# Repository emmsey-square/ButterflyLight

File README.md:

# ButterflyLight
Butterfly-shaped keychain thing with addressable leds

### Front PCB with decorative silkscreen and solder mask cutouts

### Back PCB with components and battery holder

### Schematic for back PCB

## Design Choices 
* CH32V003 in SOIC 8 package-low cost, great SDk courtesy of cnLohr: [ch32fun](https://github.com/cnlohr/ch32fun)
* CR2032 battery holder on back
* Switching regulator to convert battery voltage to suitable 5V for leds

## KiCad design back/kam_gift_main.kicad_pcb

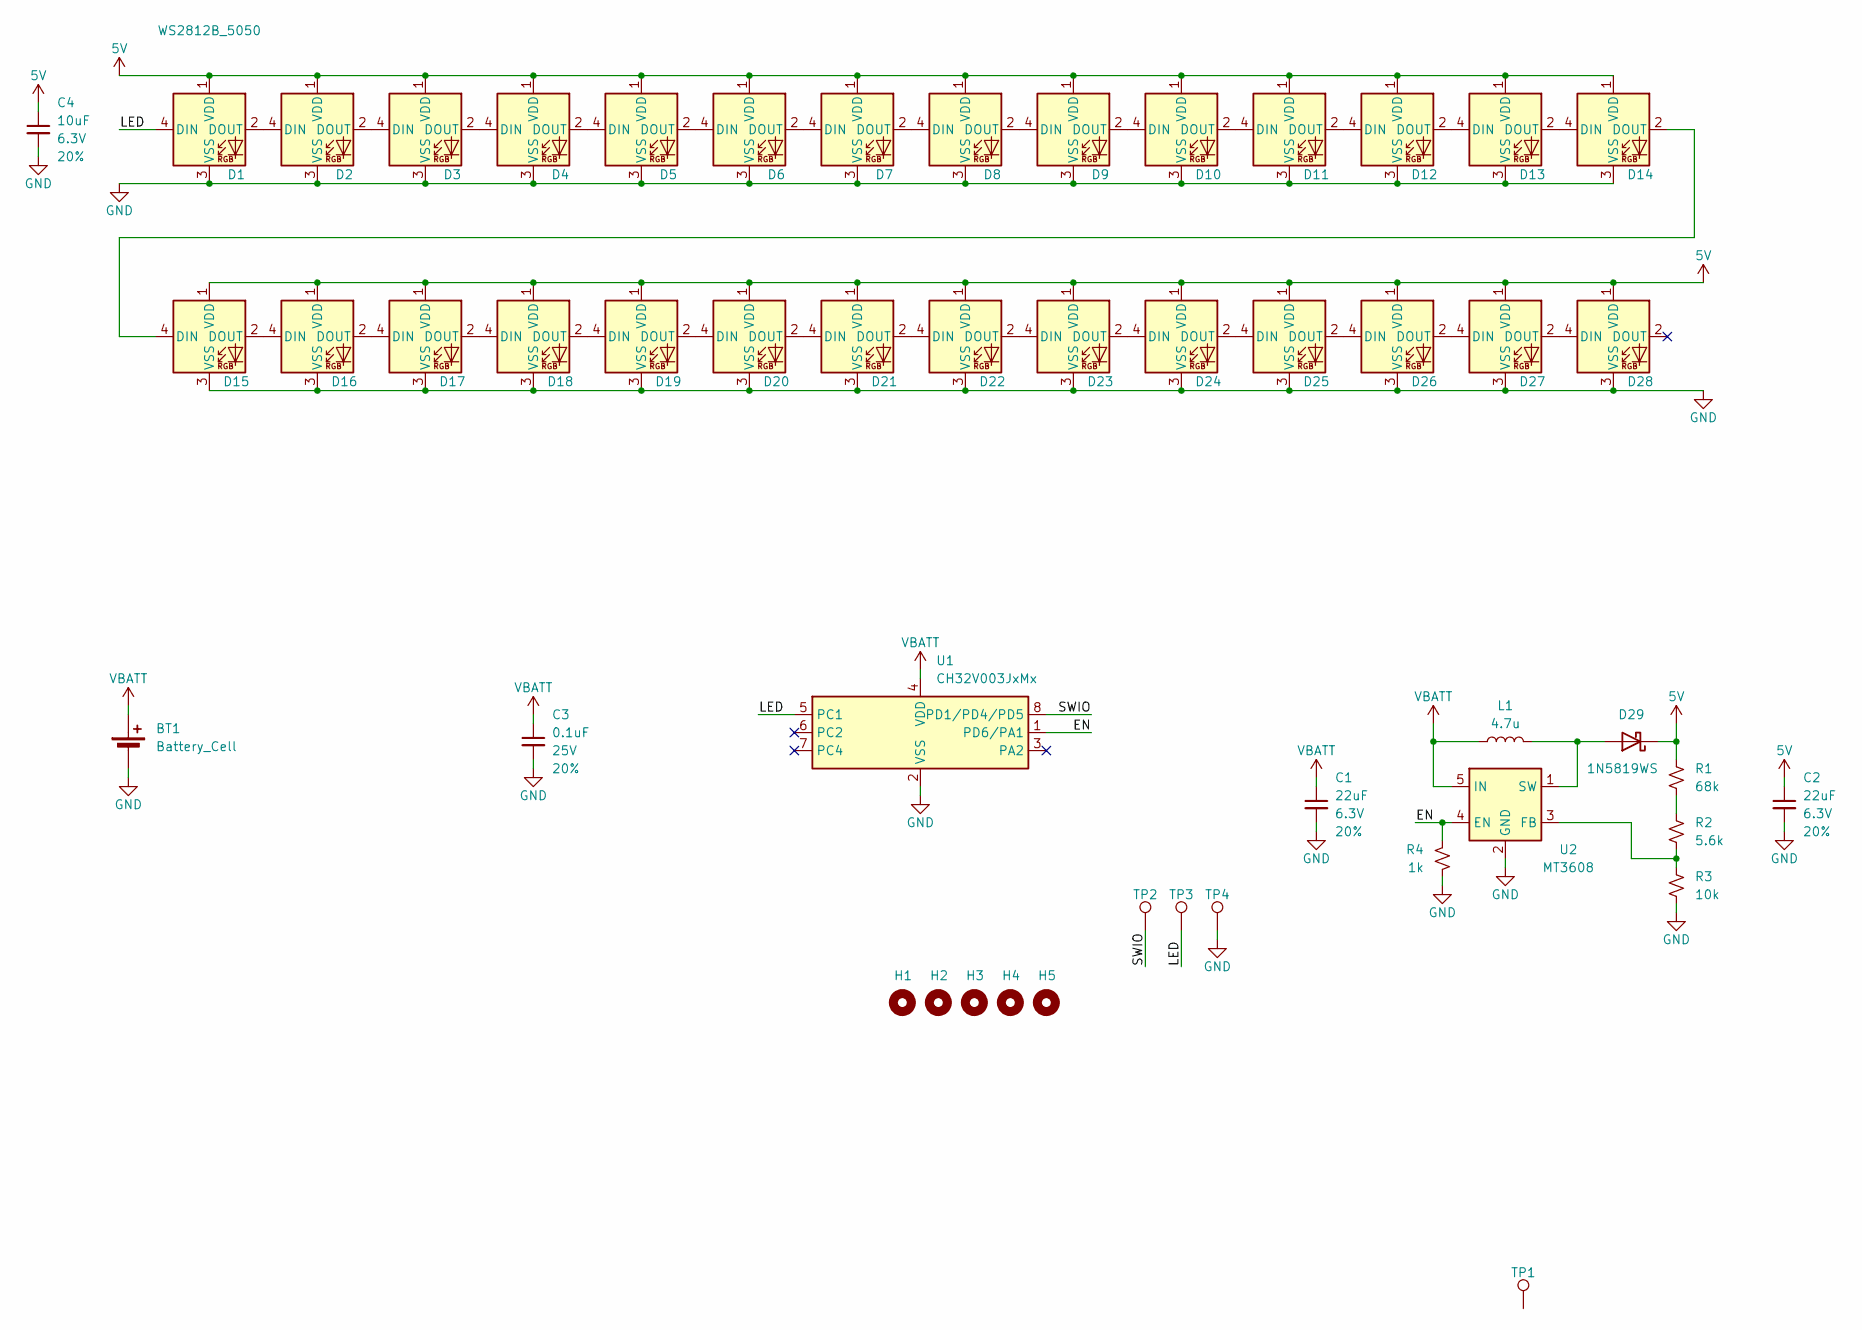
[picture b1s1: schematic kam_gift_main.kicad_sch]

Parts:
BT1: Battery_Cell; BatteryHolder_Multicomp_BC-2001_1x2032
C1, C2: 22uF; C_0603_1608Metric; Voltage 6.3V; Tolerance 20%
C3: 0.1uF; C_0603_1608Metric; Voltage 25V; Tolerance 20%
C4: 10uF; C_0603_1608Metric; Voltage 6.3V; Tolerance 20%
D1, D2, D3, D4, D5, D6, D7, D8, D9, D10, D11, D12, D13, D14, D15, D16, D17, D18, D19, D20, D21, D22, D23, D24, D25, D26, D27, D28: WS2812B_5050; LED_WS2812B_PLCC4_5.0x5.0mm_P3.2mm
D29: 1N5819WS; D_SOD-323_HandSoldering
H1, H2, H3, H4: MountingHole; MountingHole_3.2mm_M3
H5: MountingHole; MountingHole_2.2mm_M2
L1: 4.7u; L_1206_3216Metric_Pad1.22x1.90mm_HandSolder
R1: 68k; R_0603_1608Metric
R2: 5.6k; R_0603_1608Metric
R3: 10k; R_0603_1608Metric
R4: 1k; R_0603_1608Metric
TP1, TP2, TP3, TP4: 1.25mm; TestPoint_Pad_D3.0mm
U1: CH32V003JxMx; JEITA_SOIC-8_3.9x4.9mm_P1.27mm
U2: MT3608; SOT-23-6

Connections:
5V: C2.1, C4.1, D1.1 (VDD), D2.1 (VDD), D3.1 (VDD), D4.1 (VDD), D5.1 (VDD), D6.1 (VDD), D7.1 (VDD), D8.1 (VDD), D9.1 (VDD), D10.1 (VDD), D11.1 (VDD), D12.1 (VDD), D13.1 (VDD), D14.1 (VDD), D15.1 (VDD), D16.1 (VDD), D17.1 (VDD), D18.1 (VDD), D19.1 (VDD), D20.1 (VDD), D21.1 (VDD), D22.1 (VDD), D23.1 (VDD), D24.1 (VDD), D25.1 (VDD), D26.1 (VDD), D27.1 (VDD), D28.1 (VDD), D29.1 (K), R1.2
/EN: R4.2, U1.1 (PD6/PA1), U2.4 (EN)
/LED: D1.4 (DIN), TP3.1, U1.5 (PC1); also elsewhere on the board
/SWIO: TP2.1, U1.8 (PD1/PD4/PD5); also elsewhere on the board
GND: BT1.2 (-), C1.2, C2.2, C3.2, C4.2, D1.3 (VSS), D2.3 (VSS), D3.3 (VSS), D4.3 (VSS), D5.3 (VSS), D6.3 (VSS), D7.3 (VSS), D8.3 (VSS), D9.3 (VSS), D10.3 (VSS), D11.3 (VSS), D12.3 (VSS), D13.3 (VSS), D14.3 (VSS), D15.3 (VSS), D16.3 (VSS), D17.3 (VSS), D18.3 (VSS), D19.3 (VSS), D20.3 (VSS), D21.3 (VSS), D22.3 (VSS), D23.3 (VSS), D24.3 (VSS), D25.3 (VSS), D26.3 (VSS), D27.3 (VSS), D28.3 (VSS), R3.1, R4.1, TP4.1, U1.2 (VSS), U2.2 (GND); also elsewhere on the board
unnamed: D1.2 (DOUT), D2.4 (DIN)
unnamed: D2.2 (DOUT), D3.4 (DIN)
unnamed: D3.2 (DOUT), D4.4 (DIN)
unnamed: D4.2 (DOUT), D5.4 (DIN)
unnamed: D5.2 (DOUT), D6.4 (DIN)
unnamed: D6.2 (DOUT), D7.4 (DIN)
unnamed: D7.2 (DOUT), D8.4 (DIN)
unnamed: D8.2 (DOUT), D9.4 (DIN)
unnamed: D9.2 (DOUT), D10.4 (DIN)
unnamed: D10.2 (DOUT), D11.4 (DIN)
unnamed: D11.2 (DOUT), D12.4 (DIN)
unnamed: D12.2 (DOUT), D13.4 (DIN)
unnamed: D13.2 (DOUT), D14.4 (DIN)
unnamed: D14.2 (DOUT), D15.4 (DIN)
unnamed: D15.2 (DOUT), D16.4 (DIN)
unnamed: D16.2 (DOUT), D17.4 (DIN)
unnamed: D17.2 (DOUT), D18.4 (DIN)
unnamed: D18.2 (DOUT), D19.4 (DIN)
unnamed: D19.2 (DOUT), D20.4 (DIN)
unnamed: D20.2 (DOUT), D21.4 (DIN)
unnamed: D21.2 (DOUT), D22.4 (DIN)
unnamed: D22.2 (DOUT), D23.4 (DIN)
unnamed: D23.2 (DOUT), D24.4 (DIN)
unnamed: D24.2 (DOUT), D25.4 (DIN)
unnamed: D25.2 (DOUT), D26.4 (DIN)
unnamed: D26.2 (DOUT), D27.4 (DIN)
unnamed: D27.2 (DOUT), D28.4 (DIN)
unnamed: D29.2 (A), L1.2, U2.1 (SW)
unnamed: R1.1, R2.2
unnamed: R2.1, R3.2, U2.3 (FB)
VBATT: BT1.1 (+), C1.1, C3.1, L1.1, U1.4 (VDD), U2.5 (IN)

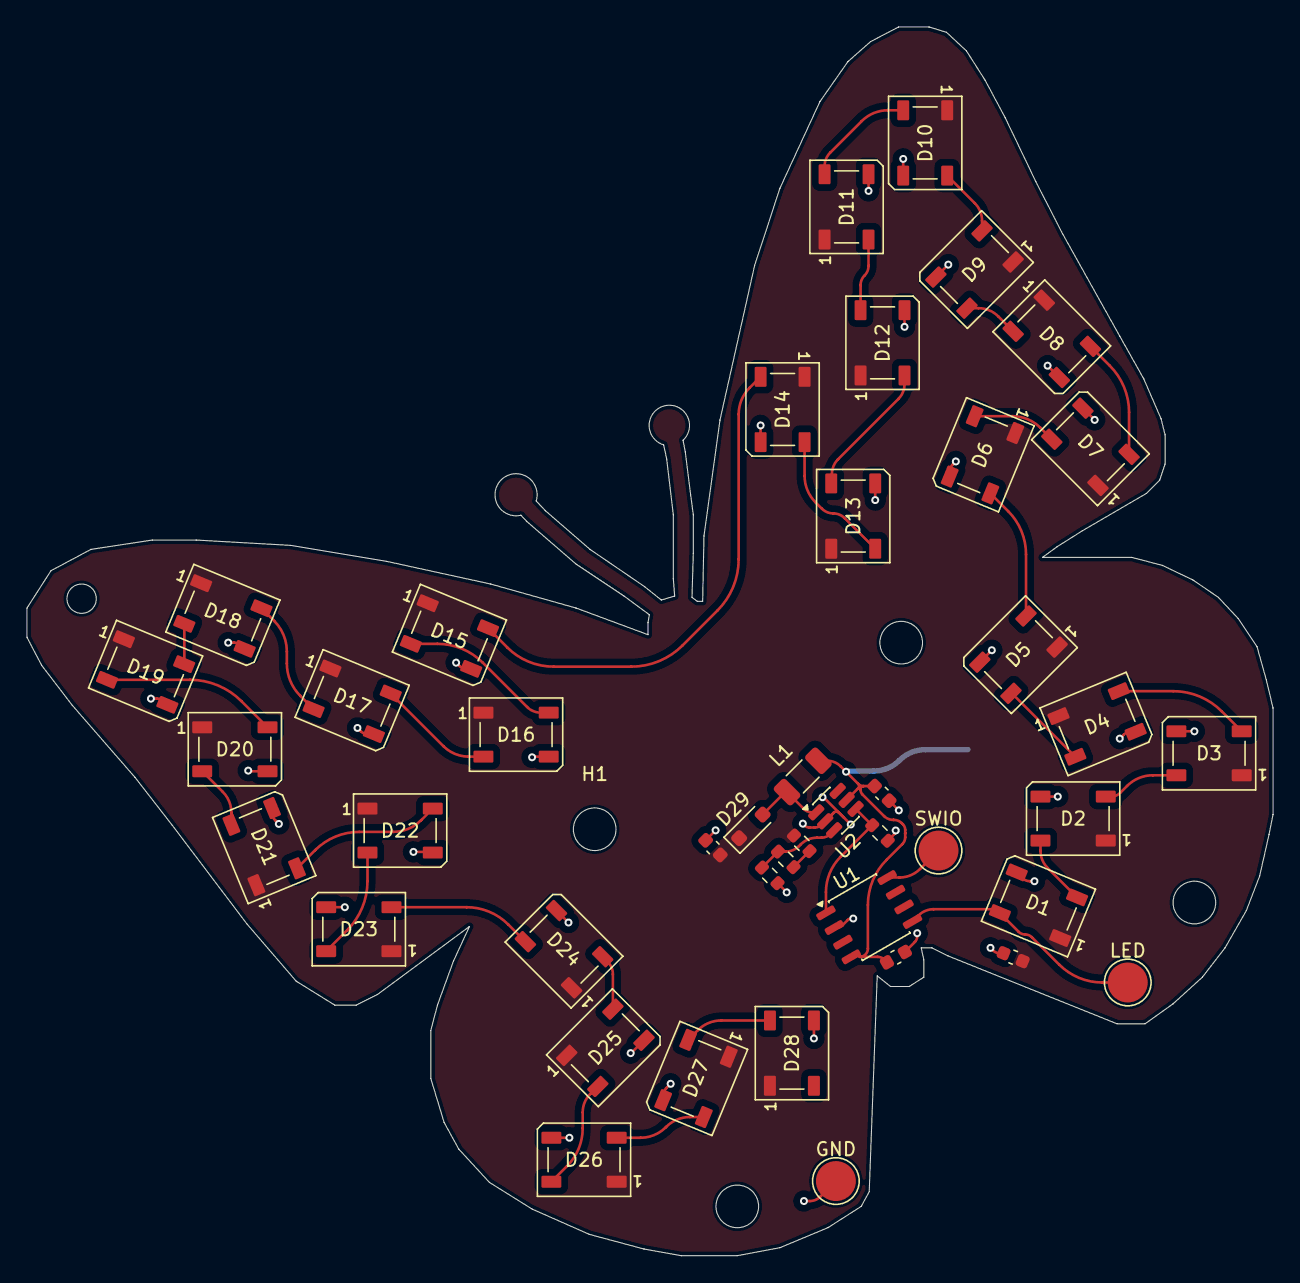
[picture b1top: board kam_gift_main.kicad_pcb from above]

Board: 2 copper layers, 93.5 x 92.2 mm, 49 parts (1 on the bottom side), 36 nets.

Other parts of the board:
GND: 1.25mm; TestPoint_Pad_D3.0mm
LED: 1.25mm; TestPoint_Pad_D3.0mm
SWIO: 1.25mm; TestPoint_Pad_D3.0mm

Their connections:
/LED: LED.1; also elsewhere on the board
/SWIO: SWIO.1; also elsewhere on the board
GND: GND.1; also elsewhere on the board

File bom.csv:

"Id";"Designator";"Footprint";"Quantity";"Designation";"Supplier and ref";
1;"D19,D18,D28,D27,D25,D6,D4,D3,D15,D1,D21,D9,D2,D16,D23,D14,D22,D24,D8,D7,D11,D5,D13,D17,D12,D20,D10,D26";"LED_WS2812B_PLCC4_5.0x5.0mm_P3.2mm";28;"WS2812B_5050";;;
2;"LED,GND,SWIO";"TestPoint_Pad_D3.0mm";3;"1.25mm";;;
3;"C2,C1";"C_0603_1608Metric";2;"22uF";;;
4;"R1";"R_0603_1608Metric";1;"68k";;;
5;"R2";"R_0603_1608Metric";1;"5.6k";;;
6;"D29";"D_SOD-323_HandSoldering";1;"1N5819WS";;;
7;"C4";"C_0603_1608Metric";1;"10uF";;;
8;"U1";"JEITA_SOIC-8_3.9x4.9mm_P1.27mm";1;"CH32V003JxMx";;;
9;"C3";"C_0603_1608Metric";1;"0.1uF";;;
10;"R3";"R_0603_1608Metric";1;"10k";;;
11;"R4";"R_0603_1608Metric";1;"1k";;;
12;"U2";"SOT-23-6";1;"MT3608";;;
13;"L1";"L_1206_3216Metric_Pad1.22x1.90mm_HandSolder";1;"4.7u";;;
14;"BT1";"BatteryHolder_Multicomp_BC-2001_1x2032";1;"Battery_Cell";;;

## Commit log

2026-06-23 Add images to README
2026-06-23 Updated README
    Added detailed sections for front and back PCBs, schematic, and design choices.
